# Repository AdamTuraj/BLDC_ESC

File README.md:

# BLDC ESC

**25A 8.4V Sensored BLDC Motor Driver (DRV8323 Based)**

This ESC was originally designed for my **AT25 project**, but the project was discontinued due to time and budget constraints. The board itself is theoretically still fully functional (I have not physically tested it).

- **Continuous Current:** 25A
- **Peak Current:** 50A
- **Input Voltage:** 8.4V (2S Li-Po)
- **Driver IC:** TI DRV8323
- **Control Mode:** Single PWM mode (simplifies control, avoids heavy math)

## Design Overview

The ESC is built around the **DRV8323** gate driver IC, making use of its 1x PWM control mode for easier firmware integration.

## Renders & Schematics

### 3D Renders

### Electrical Schematic

### PCB Layout (4-Layer Stackup)

- **Top Layer (Signals)**  
  .png)

- **Second Layer (Ground Plane)**  
  .png)

- **Third Layer (Power / Signals)**  
  .png)

- **Bottom Layer (Signals)**  
  .png)

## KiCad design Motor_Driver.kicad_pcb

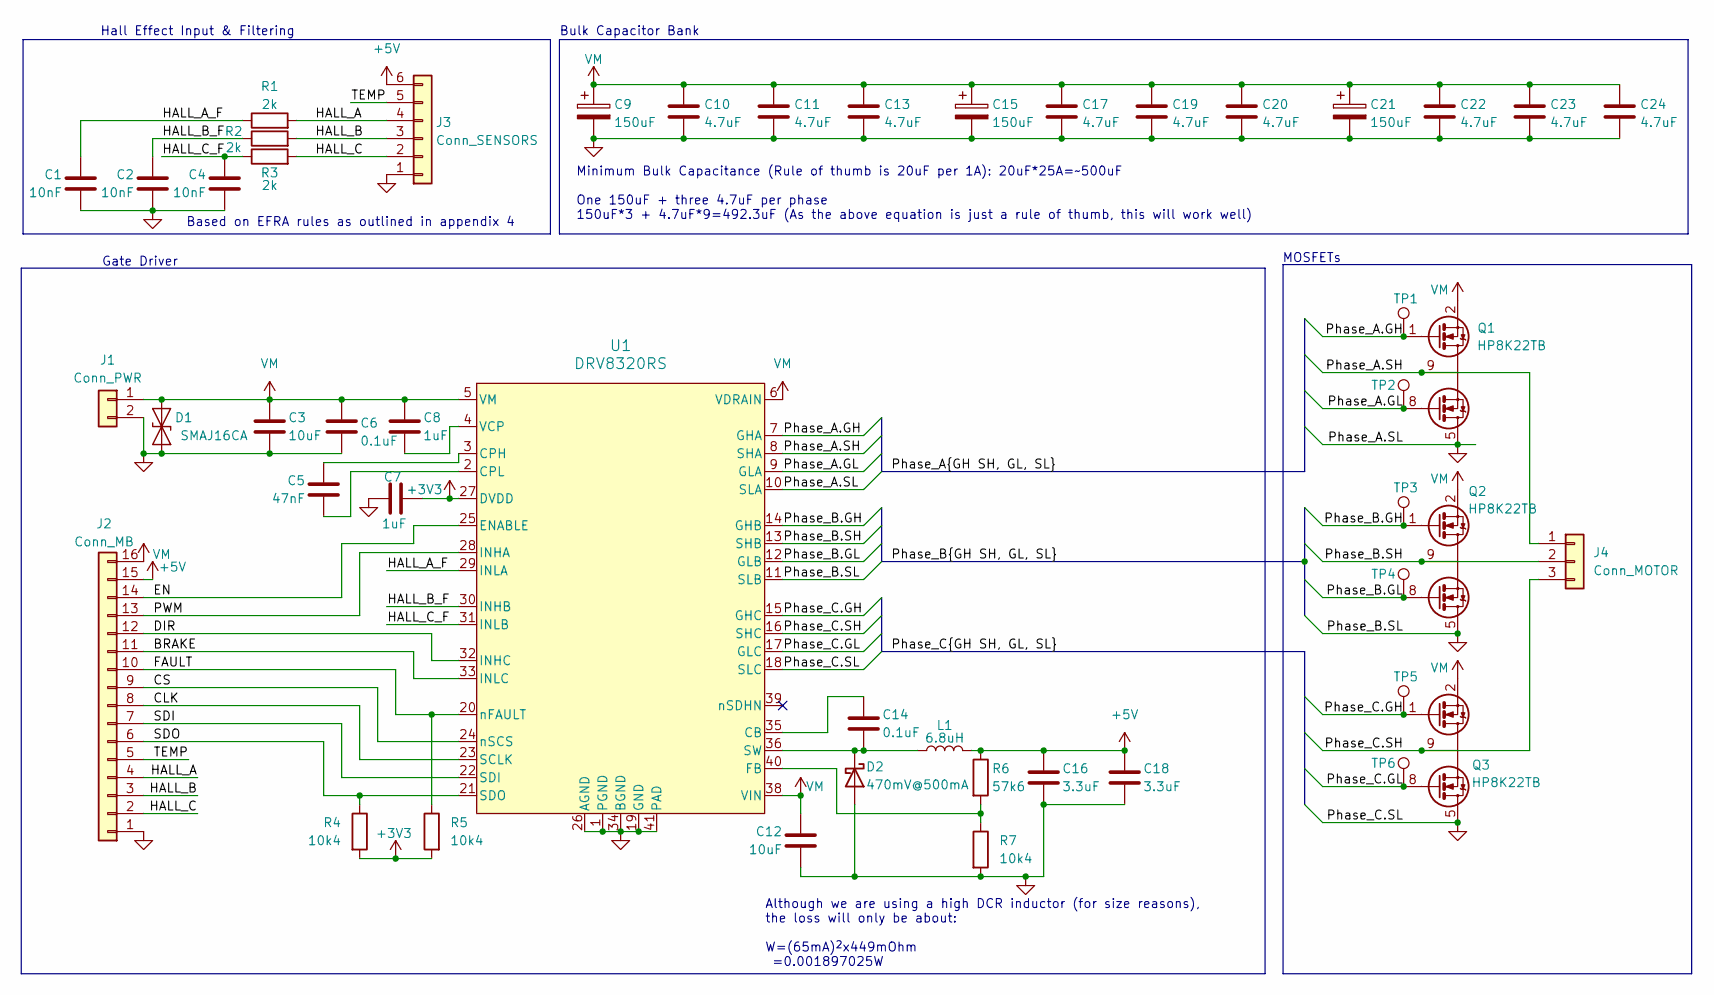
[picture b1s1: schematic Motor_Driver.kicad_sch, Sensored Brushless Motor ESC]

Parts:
C1, C2, C4: 10nF; C_0603_1608Metric; MPN CL10B103KO8WPNC
C3, C12: 10uF; C_0603_1608Metric; MPN GRM188C81C106MA73D
C5: 47nF; C_0603_1608Metric
C6, C14: 0.1uF; C_0603_1608Metric; MPN CC0603KRX7R7BB104
C7, C8: 1uF; C_0603_1608Metric; MPN CC0603KRX7R7BB105
C9, C15, C21: 150uF; CP_Elec_8x6.9; MPN APXN160ARA151MH70G
C10, C11, C13, C17, C19, C20, C22, C23, C24: 4.7uF; C_0805_2012Metric; MPN CL21B475KOFNNNE
C16, C18: 3.3uF; C_0603_1608Metric; MPN CL10A335KP8NNNC
D1: SMAJ16CA; D_SMA; MPN SMAJ16CA-13-F
D2: 470mV@500mA; D_SOD-323; MPN CMDSH05-4 TR PBFREE
J1: Conn_PWR; AMASS_XT60PW-M_1x02_P7.20mm_Horizontal
J2: Conn_MB; PinSocket_2x08_P2.54mm_Vertical; MPN 10129381-916001BLF
J3: Conn_SENSORS; JST_ZH_B6B-ZR_1x06_P1.50mm_Vertical; MPN B6B-XH-A
J4: Conn_MOTOR; Pin_Bullet_D4.7mm
L1: 6.8uH; L_Vishay_IHLP-1212; MPN LQH3NPN6R8MMEL
Q1, Q2, Q3: HP8K22TB; HP8K24TB; MPN HP8K22TB
R1, R2, R3: 2k; R_0603_1608Metric; MPN RK73B1JTTD202J
R4, R5, R7: 10k4; R_0603_1608Metric; MPN RT0603BRD0710K4L
R6: 57k6; R_0603_1608Metric; MPN RC0603FR-0757K6L
TP1, TP2, TP3, TP4, TP5, TP6: TestPoint; TestPoint_Pad_D1.0mm
U1: DRV8320RS; VQFN-40-1EP_6x6mm_P0.5mm_EP3.5x3.5mm_ThermalVias; MPN DRV8320RSRHAT

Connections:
+3V3: C7.1, R4.2, R5.2, U1.27 (DVDD)
+5V: C16.1, C18.1, J2.15, J3.6, L1.2, R6.1
/BRAKE: J2.11, U1.33 (INLC)
/CLK: J2.8, U1.23 (SCLK)
/CS: J2.9, U1.24 (nSCS)
/DIR: J2.12, U1.32 (INHC)
/EN: J2.14, U1.25 (ENABLE)
/FAULT: J2.10, R5.1, U1.20 (nFAULT)
/HALL_A: J2.4, J3.4, R1.2
/HALL_A_F: C1.1, R1.1, U1.29 (INLA)
/HALL_B: J2.3, J3.3, R2.2
/HALL_B_F: C2.1, R2.1, U1.30 (INHB)
/HALL_C: J2.2, J3.2, R3.2
/HALL_C_F: C4.1, R3.1, U1.31 (INLB)
/PWM: J2.13, U1.28 (INHA)
/Phase_A.GH: Q1.1 (T_{G}), TP1.1, U1.7 (GHA)
/Phase_A.GL: Q1.8 (B_{G}), TP2.1, U1.9 (GLA)
/Phase_A.SH: J4.1, Q1.9 (T_{GR}), U1.8 (SHA)
/Phase_B.GH: Q2.1 (T_{G}), TP3.1, U1.14 (GHB)
/Phase_B.GL: Q2.8 (B_{G}), TP4.1, U1.12 (GLB)
/Phase_B.SH: J4.2, Q2.9 (T_{GR}), U1.13 (SHB)
/Phase_C.GH: Q3.1 (T_{G}), TP5.1, U1.15 (GHC)
/Phase_C.GL: Q3.8 (B_{G}), TP6.1, U1.17 (GLC)
/Phase_C.SH: J4.3, Q3.9 (T_{GR}), U1.16 (SHC)
/SDI: J2.7, U1.22 (SDI)
/SDO: J2.6, R4.1, U1.21 (SDO)
/TEMP: J2.5, J3.5
GND: C1.2, C2.2, C3.2, C4.2, C6.2, C7.2, C9.2, C10.2, C11.2, C12.2, C13.2, C15.2, C16.2, C17.2, C18.2, C19.2, C20.2, C21.2, C22.2, C23.2, C24.2, D1.1 (A1), D2.2 (A), J1.2, J2.1, J3.1, Q1.5 (P_{GND}), Q1.6 (P_{GND}), Q1.7 (P_{GND}), Q2.5 (P_{GND}), Q2.6 (P_{GND}), Q2.7 (P_{GND}), Q3.5 (P_{GND}), Q3.6 (P_{GND}), Q3.7 (P_{GND}), R7.2, U1.1 (PGND), U1.10 (SLA), U1.11 (SLB), U1.18 (SLC), U1.19 (GND), U1.26 (AGND), U1.34 (BGND), U1.41 (PAD)
unnamed: C14.2, D2.1 (K), L1.1, U1.36 (SW)
unnamed: C14.1, U1.35 (CB)
unnamed: C5.1, U1.3 (CPH)
unnamed: C5.2, U1.2 (CPL)
unnamed: R6.2, R7.1, U1.40 (FB)
unnamed: C8.2, U1.4 (VCP)
VM: C3.1, C6.1, C8.1, C9.1, C10.1, C11.1, C12.1, C13.1, C15.1, C17.1, C19.1, C20.1, C21.1, C22.1, C23.1, C24.1, D1.2 (A2), J1.1, J2.16, Q1.2 (V_{IN}), Q1.3 (V_{IN}), Q1.4 (V_{IN}), Q2.2 (V_{IN}), Q2.3 (V_{IN}), Q2.4 (V_{IN}), Q3.2 (V_{IN}), Q3.3 (V_{IN}), Q3.4 (V_{IN}), U1.5 (VM), U1.6 (VDRAIN), U1.38 (VIN)

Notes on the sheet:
MOSFETs
Although we are using a high DCR inductor (for size reasons), the loss will only be about: W=(65mA)^{2}x449mOhm =0.001897025W
Hall Effect Input & Filtering
Based on EFRA rules as outlined in appendix 4
Gate Driver
Minimum Bulk Capacitance (Rule of thumb is 20uF per 1A): 20uF*25A=~500uF One 150uF + three 4.7uF per phase 150uF*3 + 4.7uF*9=492.3uF (As the above equation is just a rule of thumb, this will work well)
Bulk Capacitor Bank

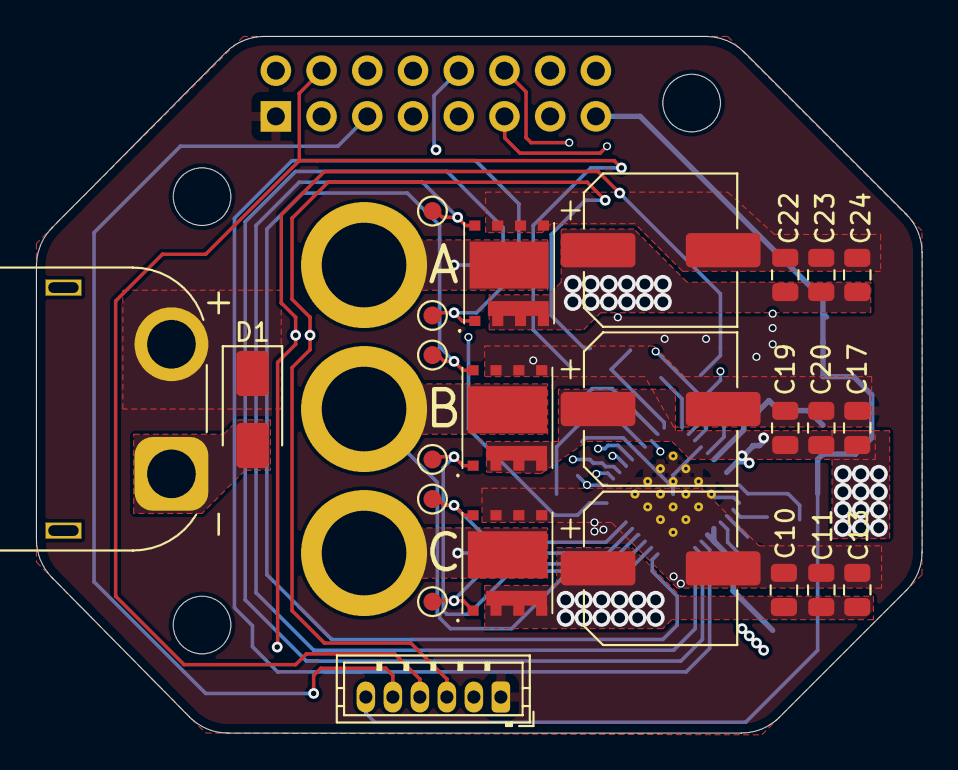
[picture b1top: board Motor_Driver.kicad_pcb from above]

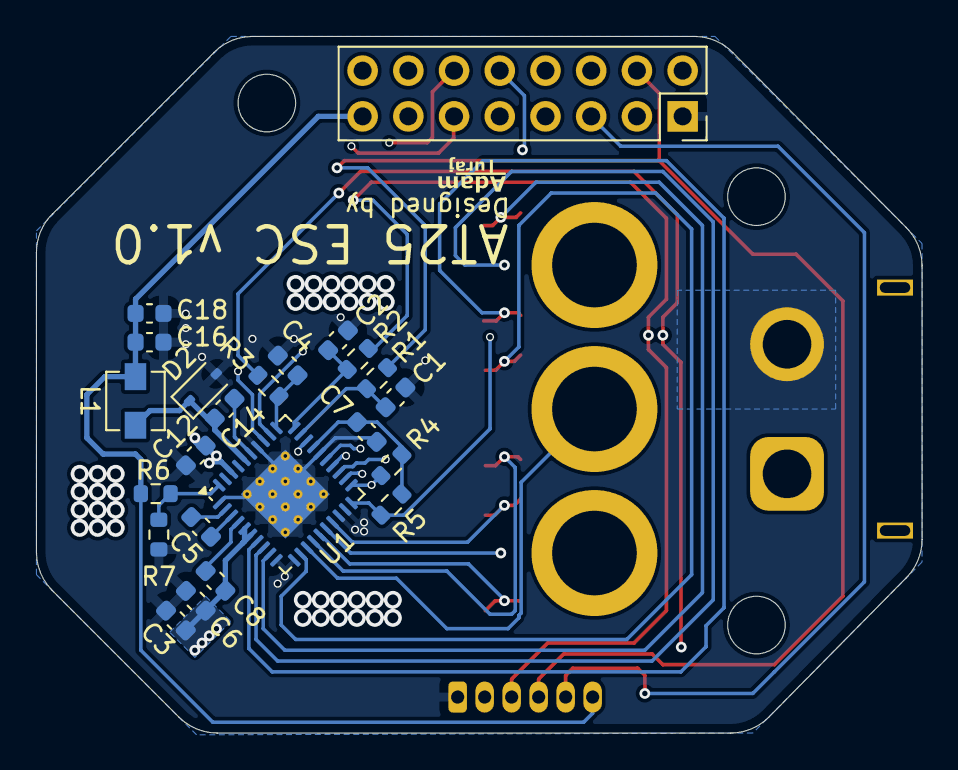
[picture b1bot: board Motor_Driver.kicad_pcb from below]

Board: 4 copper layers, 49.2 x 38.7 mm, 48 parts (23 on the bottom side), 35 nets.

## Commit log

2026-03-10 Replace external image links with local paths
    Updated image links in README to local paths.
